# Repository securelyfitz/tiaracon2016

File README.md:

# Tiaracon 2016 PCB badge
http://tiaracon.org/
ATtiny-based charlieplexed LED flasher derived from https://git.io/fireflies with different artwork and fancy pcb

## Hardware Description
This project is designed as the badge for tiaracon 2016. The circuit is intended to be a simple soldering project based on the ATTiny using only a handful of through-hole components. It uses 3 I/O pins to drive 6 charlieplexed LEDs, and an additional I/O pin for a mode button.

## Bill of Materials:
* 6x 3mm or 5mm LEDs with .1" spacing
* 3x 150 Ohm Resistor
* 1x ATTiny85 8-DIP
* 1x 20mm CR2032 holder and battery
* 1x 6x6mm SPST-NO mode button

In quantity, BOM cost is just over $2 (unless, like today, ATTinys are $4 each on digikey instead of $1)

##Building
All of the components are labeled right on the board. The ATTiny goes on the BACK of the board, the side with the ponys. Note the location of pin 1. All other components can go on either side, though it seems like LEDS on front and everything else on the back looks best.

##Software Description
This code is an Arduino sketch. I used the Sparkfun TinyAVR Programmer and follow the linked hookup guide to get it working: https://www.sparkfun.com/products/11801

The code for lighting the Charlieplexed LED's is cut and pasted from Jason Webb's project linked above. The code for sensing the capacitive buttons is based on Paul Stoffregen's updated CapacitiveSensor libarry: https://github.com/PaulStoffregen/CapacitiveSensor 

I rely heavily on global variables, and use the state and values to determine what to display on any given iteration. This allows me to responsively check the capsense button without dealing with interrupts.

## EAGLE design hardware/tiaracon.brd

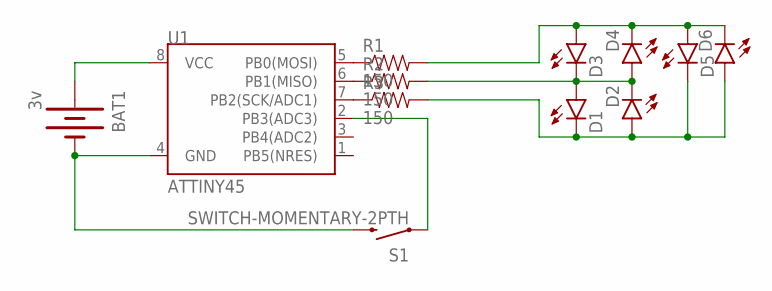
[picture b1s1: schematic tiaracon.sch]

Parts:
BAT1: 3v; BATTCOM_20MM_PTH
D1, D2, D3, D4, D5, D6: LED3MM
R1, R2, R3: 150; AXIAL-0.4
S1: SWITCH-MOMENTARY-2PTH; TACTILE-PTH
U1: ATTINY45; DIP08

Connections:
GND: BAT1.2 (-), S1.3 (2), U1.4 (GND)
unnamed: R1.P$1 (1), U1.5 (PB0(MOSI))
unnamed: R2.P$1 (1), U1.6 (PB1(MISO))
unnamed: R3.P$1 (1), U1.7 (PB2(SCK/ADC1))
unnamed: S1.1, U1.2 (PB3(ADC3))
unnamed: D3.A, D4.K (C), D5.A, D6.K (C), R1.P$2 (2)
unnamed: D1.K (C), D2.A, D5.K (C), D6.A, R3.P$2 (2)
unnamed: D1.A, D2.K (C), D3.K (C), D4.A, R2.P$2 (2)
VCC: BAT1.1 (+), U1.8 (VCC)

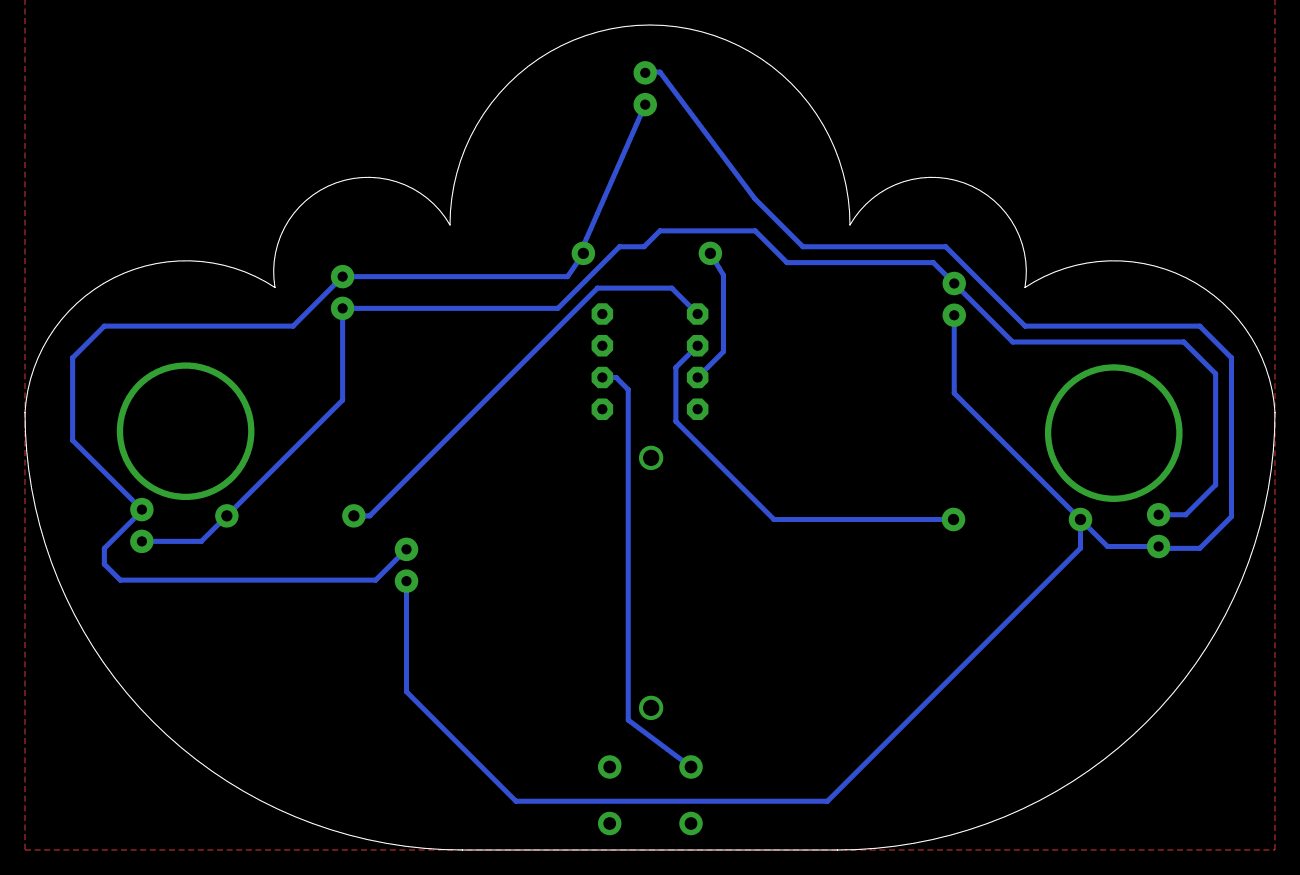
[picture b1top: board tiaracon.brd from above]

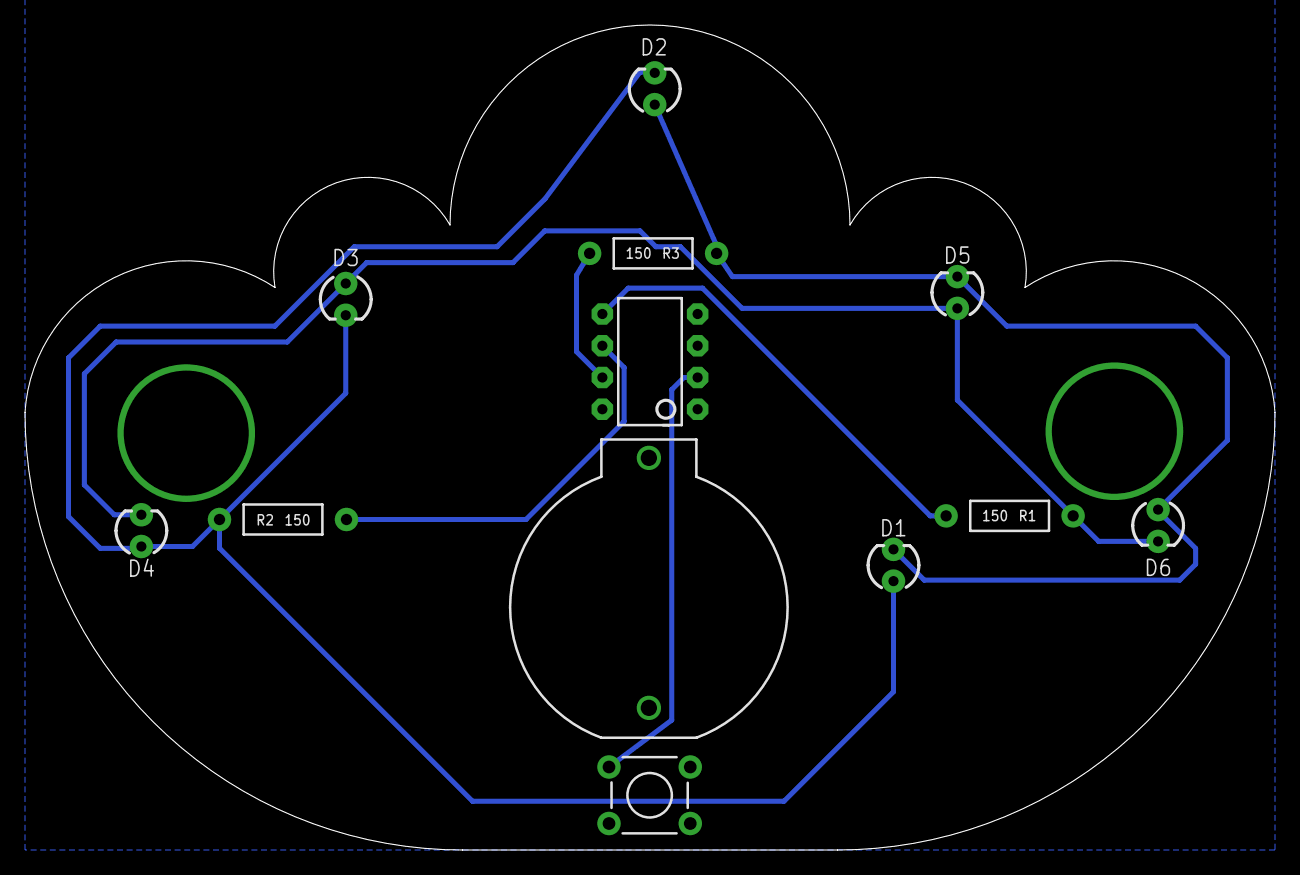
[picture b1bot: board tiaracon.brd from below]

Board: 2 copper layers, 100.0 x 66.0 mm, 14 parts (13 on the bottom side), 9 nets.

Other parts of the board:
U$1: TIARA
U$2: PONY

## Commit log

2016-07-09 updating filenames
2016-07-09 adding tiara artwork, inital attempt at rough layout of components. No traces yet.
2016-07-09 first rev of oval badge
2016-07-09 changed to scalloped badge edge
2016-07-09 adjusted spacing and alignment, adjusted lanyard hole size - probably too big
2016-07-09 including updated brd and sch files. changed switch to through hole, etc
2016-07-09 circuit laid out, added ponies and text. still need to adjust lanyard holes
2016-07-09 final draft. need comments on colors, lanyard hole placement, and text
2016-07-10 final round of changes, pcb to be ordered if approved...
2016-07-20 fix arduino sketch to use pushbutton instead of touch sensorwqwq
2016-07-22 major software rewrite: -button triggered by interrupt, not polling -reordered commands in analogOn(), putting low/ground values first to avoid charge leakage resulting in random flashing of other le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
2016-07-22 adjusted silkscreen and added note on how to orient LEDs when assembling.
2016-07-23 all todos completed, including: -fixed some spurious flashing due to poorly ordered charlieplexing commands -fixed slow flash mode to be interruptable -fixed sleep mode to not immediately wake up on 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

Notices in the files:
parts and their libraries:
SparkFun-Electromechanical: Licensing: Creative Commons ShareAlike 4.0 International - https://creativecommons.org/licenses/by-sa/4.0
